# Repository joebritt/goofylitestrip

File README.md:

# goofylitestrip

Inspired by the Radio Shack "Goofy Lite" P-Box kit, this is a strip of 5 neon (NE2) lamp relaxation
oscillators.

The lamps can be configured to flash sequentially or randomly depending on how some capacitors are
loaded.

# Power input is 90 - 120 Volts, so caution must be used!
# The author takes no responsibility for what you do with this circuit!
# Be CAREFUL!

# If you do not have experience working with high voltages, make sure you get someone experienced to help you.

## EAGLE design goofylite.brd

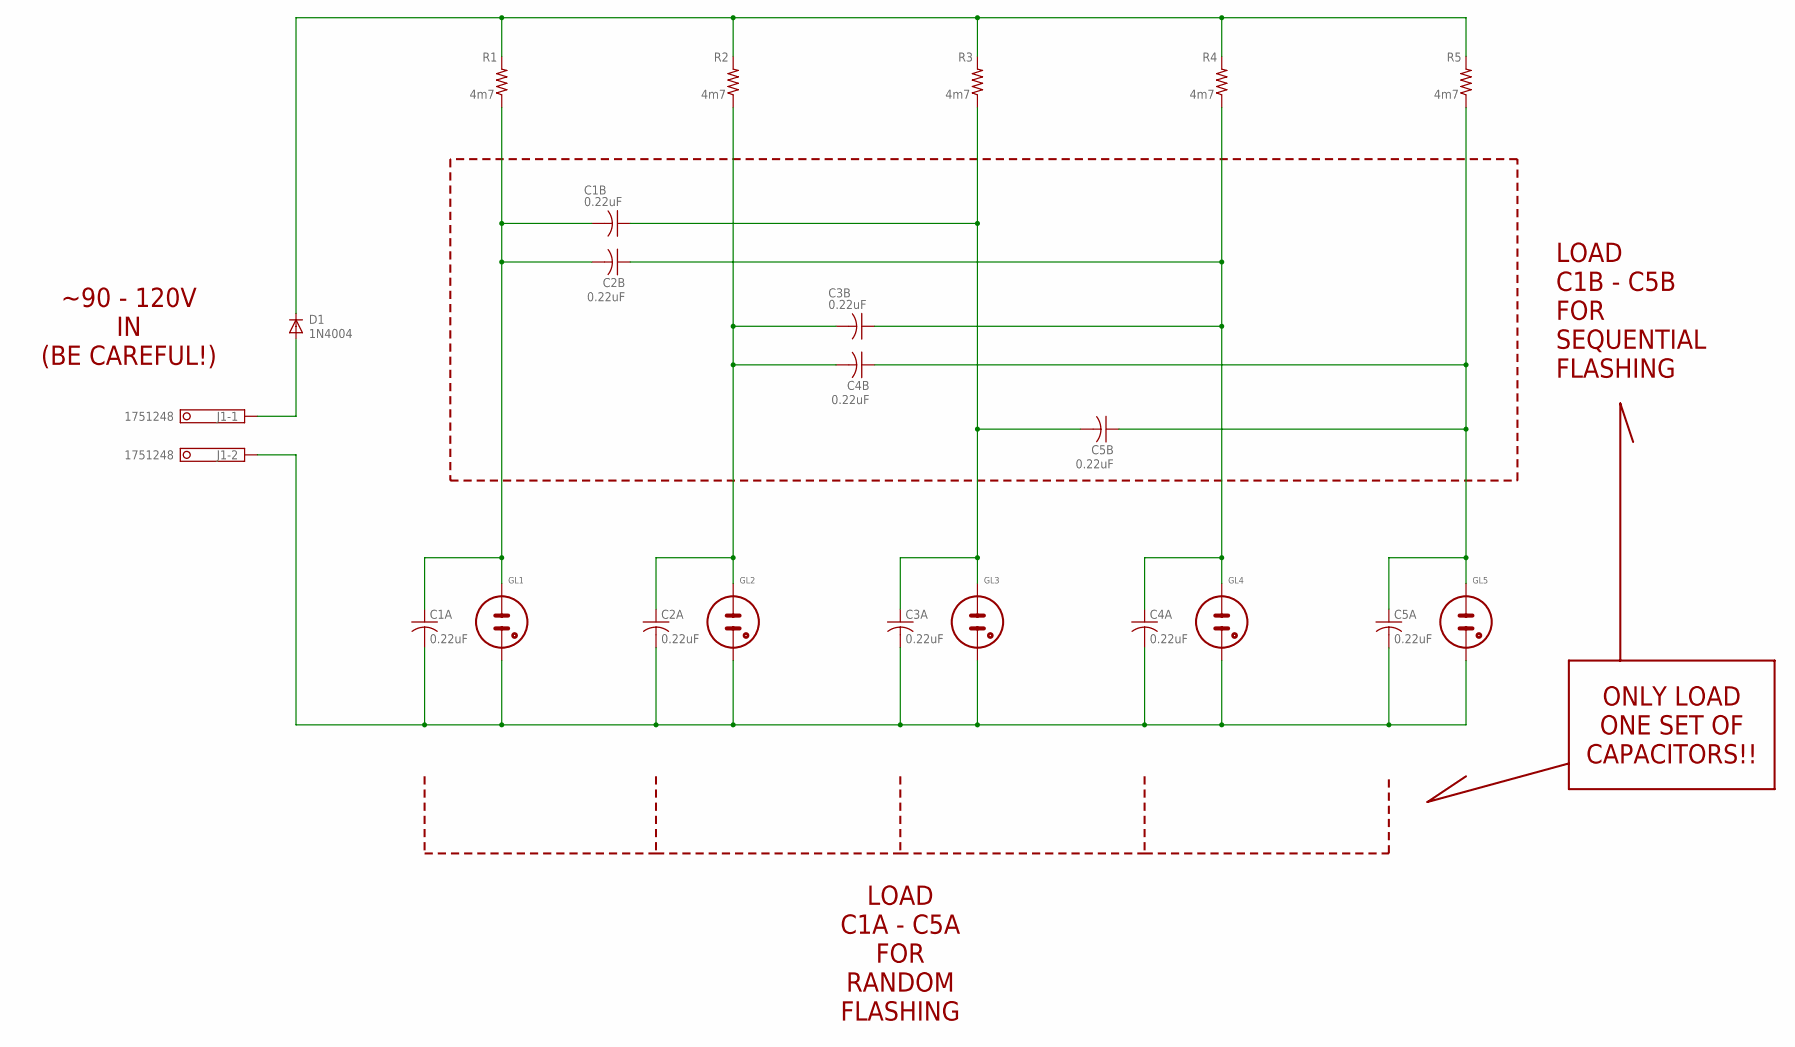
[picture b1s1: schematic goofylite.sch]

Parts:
C1A, C1B, C2A, C2B, C3A, C3B, C4A, C4B, C5A, C5B: 0.22uF; C150-054X183
D1: 1N4004; DO41-10
GL1, GL2, GL3, GL4, GL5: NE2-NEON-BULB-DRILL
J1: 1751248
R1, R2, R3, R4, R5: 4m7; 0204/7

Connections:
unnamed: C1A.1, C1B.2, C2B.2, GL1.1 (A), R1.1
unnamed: D1.C, R1.2, R2.2, R3.2, R4.2, R5.2
unnamed: C2A.1, C3B.2, C4B.2, GL2.1 (A), R2.1
unnamed: C1A.2, C2A.2, C3A.2, C4A.2, C5A.2, GL1.2 (A1), GL2.2 (A1), GL3.2 (A1), GL4.2 (A1), GL5.2 (A1), J1.2
unnamed: C1B.1, C3A.1, C5B.2, GL3.1 (A), R3.1
unnamed: C2B.1, C3B.1, C4A.1, GL4.1 (A), R4.1
unnamed: C4B.1, C5A.1, C5B.1, GL5.1 (A), R5.1
unnamed: D1.A, J1.1

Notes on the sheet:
LOAD C1B - C5B FOR SEQUENTIAL FLASHING
LOAD C1A - C5A FOR RANDOM FLASHING
~90 - 120V IN (BE CAREFUL!)
ONLY LOAD ONE SET OF CAPACITORS!!

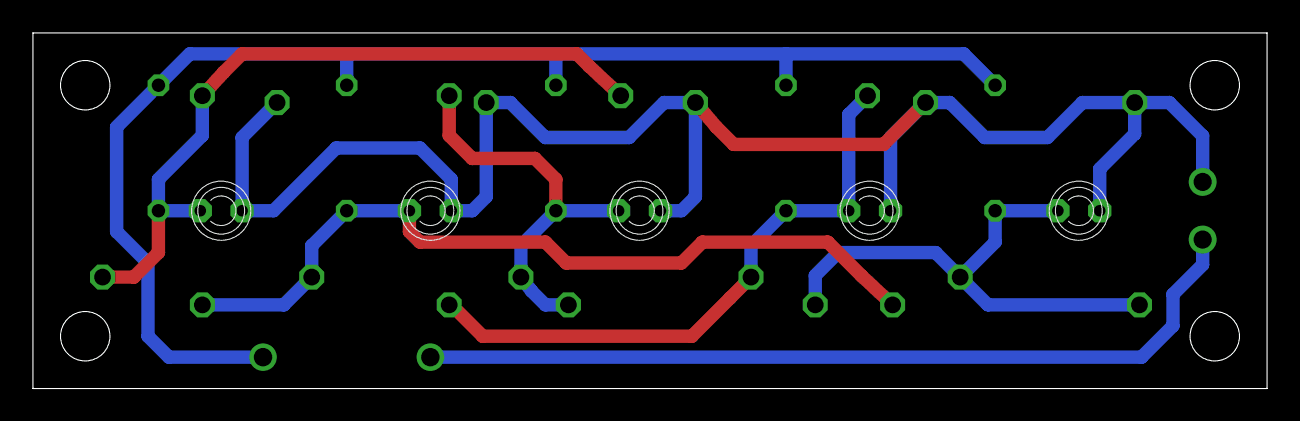
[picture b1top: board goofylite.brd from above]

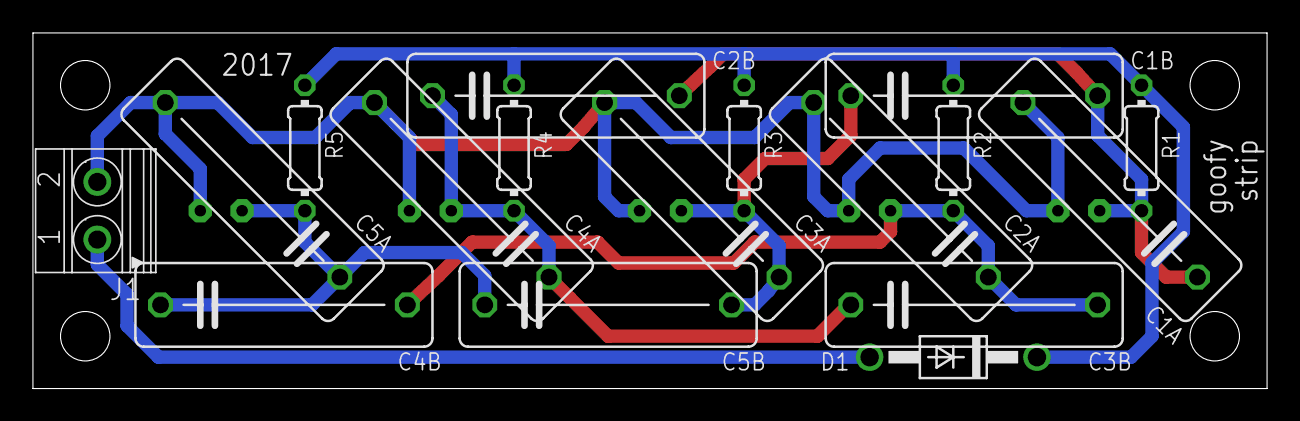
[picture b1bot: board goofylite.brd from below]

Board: 2 copper layers, 74.9 x 21.6 mm, 22 parts (17 on the bottom side), 8 nets.
